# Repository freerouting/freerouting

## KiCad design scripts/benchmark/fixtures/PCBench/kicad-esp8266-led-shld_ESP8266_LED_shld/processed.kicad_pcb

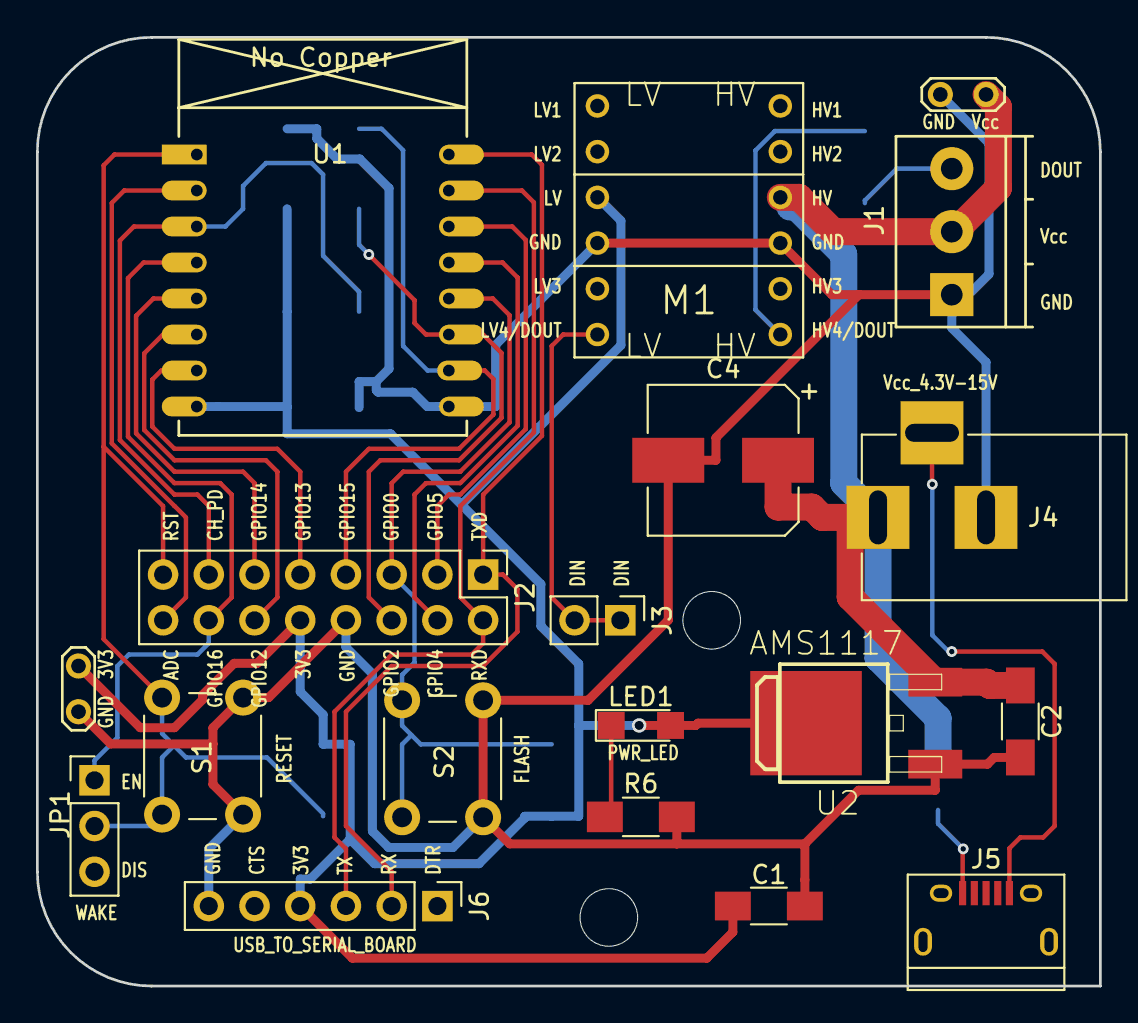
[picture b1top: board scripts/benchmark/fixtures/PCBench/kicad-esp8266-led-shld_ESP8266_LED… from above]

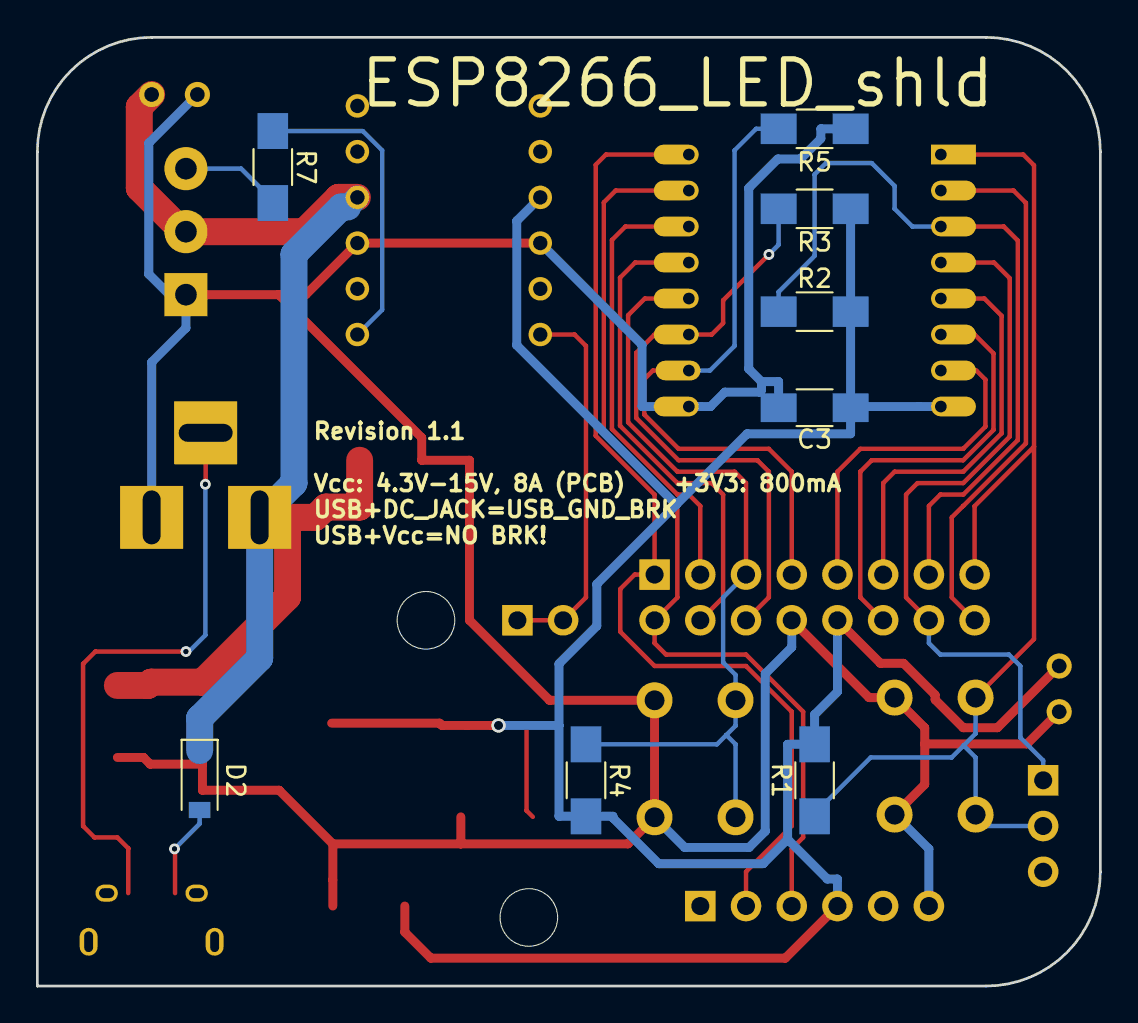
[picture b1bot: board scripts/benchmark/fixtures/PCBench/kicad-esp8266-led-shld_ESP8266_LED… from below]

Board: 2 copper layers, 59.1 x 52.7 mm, 29 parts (8 on the bottom side), 23 nets.

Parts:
C1, C2, C3: 220uF; C_1206_HandSoldering
C4: 470uF; CP_Elec_8x10
D2: DIODE; D_SOD-123
J1: Pwr_Dat_Out; TerminalBlock_Pheonix_PT-3.5mm_3pol
J2: CONN_02X08; Pin_Header_Straight_2x08_Pitch2.54mm
J3: CONN_DIN; Pin_Header_Straight_1x02_Pitch2.54mm
J4: BARREL_JACK
J5: USB-MICROB; USB_Micro-B-revision2
J6: CONN_01X06; Pin_Header_Straight_1x06_Pitch2.54mm
JP1: Jumper; Pin_Header_Straight_1x03_Pitch2.54mm
LED1: LED1206; LED_1206
M1: LOGIC_LEVEL_CONVERTER; LOGIC_LEVEL_CONVERTER-revision2
MH1, MH2: MountingHole_3.2mm_M3
R1, R2, R3, R4, R5: 10K; R_1206_HandSoldering
R6: 65; R_1206_HandSoldering
R7: 1K; R_1206_HandSoldering
S1: RESET; SW_PUSH_6mm
S2: FLASH; SW_PUSH_6mm
T1, T1_2: Test_Point_2Pads
U1: ESP-07v2
U2: AMS1117; V-REG_DPACK-revision2

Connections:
+3V3: C1.1, C3.1, J2.10, J6.4, LED1.2, M1.P$3, R1.2, R2.2, R3.1, R4.2, T1.1, U1.8, U2.2
ADC: J2.16, U1.2
CH_PD: J2.13, R2.1, U1.3
DIN: J3.1, J3.2, M1.P$6
DOUT: J1.3, R7.2
GND: C1.2, C2.2, C3.2, C4.2, J1.1, J2.8, J4.2, J6.6, M1.P$4, M1.P$9, R5.1, R6.2, S1.2, S2.2, T1.2, T1_2.2, U1.9, U2.1
GNDBREAK: J4.3, J5.GND
GPIO0: J2.5, R4.1, S2.1, U1.12
GPIO2: J2.6, R3.2, U1.11
GPIO4: J2.4, U1.13
GPIO5: J2.3, U1.14
GPIO12: J2.12, U1.6
GPIO13: J2.9, U1.7
GPIO14: J2.11, U1.5
GPIO15: J2.7, R5.2, U1.10
GPIO16: J2.14, JP1.1, U1.4
unnamed: D2.2, J5.VBUS
unnamed: LED1.1, R6.1
unnamed: M1.P$7, R7.1
REST: J2.15, JP1.2, R1.1, S1.1, U1.1
RXD: J2.2, J6.3, U1.15
TXD: J2.1, J6.2, U1.16
Vin: C2.1, C4.1, D2.1, J1.2, J4.1, M1.P$10, T1_2.1, U2.3

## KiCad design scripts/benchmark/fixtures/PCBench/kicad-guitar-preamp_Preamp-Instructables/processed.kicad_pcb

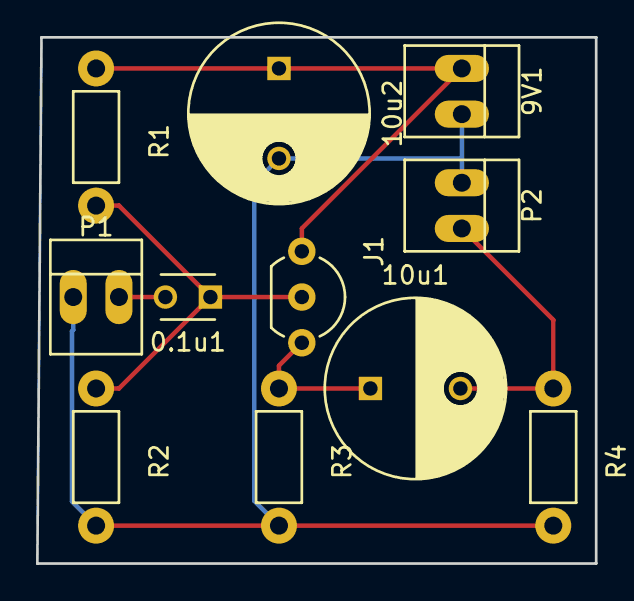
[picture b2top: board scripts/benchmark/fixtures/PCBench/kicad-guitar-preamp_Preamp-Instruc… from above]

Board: 2 copper layers, 31.0 x 29.2 mm, 11 parts (0 on the bottom side), 6 nets.

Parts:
0.1u1: C; C_Disc_D3_P2.5
9V1: Vdd; PINHEAD1-2
10u1: CP1; C_Radial_D10_L16_P5
10u2: CP2; C_Radial_D10_L16_P5
J1: 2N5457; TO-92_Inline_Wide
P1: IN; PINHEAD1-2
P2: OUT; PINHEAD1-2
R1, R2: 22M; Resistor_Horizontal_RM7mm
R3: 10k; Resistor_Horizontal_RM7mm
R4: 100k; Resistor_Horizontal_RM7mm

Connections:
GND: 9V1.2, 10u2.2, P1.1, P2.1, R2.2, R3.2, R4.2
In: 0.1u1.2, P1.2
unnamed: 0.1u1.1, J1.2, R1.2, R2.1
unnamed: 10u1.1, J1.3, R3.1
unnamed: 9V1.1, 10u2.1, J1.1, R1.1
Out: 10u1.2, P2.2, R4.1

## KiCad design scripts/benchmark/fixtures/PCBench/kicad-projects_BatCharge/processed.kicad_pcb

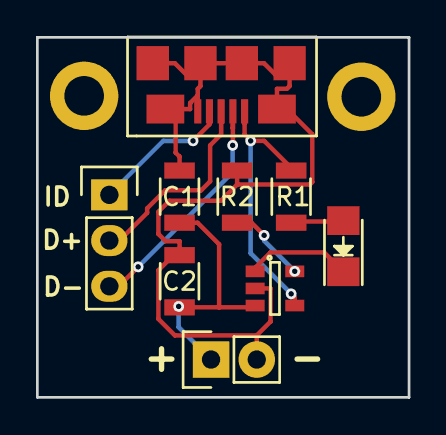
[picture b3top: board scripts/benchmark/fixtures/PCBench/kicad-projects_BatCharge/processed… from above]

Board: 2 copper layers, 20.7 x 20.0 mm, 11 parts (0 on the bottom side), 9 nets.

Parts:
C1, C2: R_1206
D1: LED; LED_1206
Noname_1: micro-usb-fci
Noname_2, Noname_3: MountingHole_2.2mm_M2_ISO14580_Pad
Noname_4: Pin_Header_Straight_1x02
Noname_5: Pin_Header_Straight_1x03
R1, R2: R_1206
U1: SOT-23-5

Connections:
GND: C1.2, C2.2, Noname_1.5, Noname_1.6, Noname_4.2, R2.2, U1.2
unnamed: C1.1, C2.1, Noname_4.1, U1.3
unnamed: D1.1, U1.1
unnamed: D1.2, R1.2
unnamed: Noname_1.4, Noname_5.1
unnamed: Noname_1.3, Noname_5.2
unnamed: Noname_1.2, Noname_5.3
unnamed: Noname_1.1, R1.1, U1.4
unnamed: R2.1, U1.5
